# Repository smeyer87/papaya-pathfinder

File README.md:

# Papaya Pathfinder — Personal Build

<div style="text-align: center;">
  
</div>

This is a personal fork of the open-source [Papaya Pathfinder](https://github.com/tronxi/papaya-pathfinder)
rover project, building the **full-size Pathfinder** with custom electronics
and a from-scratch PCB design. It is not a general-purpose reference for the
upstream project — for that (both rover variants, the Android/desktop
controllers, full parts lists, licensing), see the archived
[upstream README](docs/UPSTREAM_README.md).

This fork intentionally does **not** use `pathfinder-mini`,
`android-controller`, or `desktop-controller` — control is via a standard
R/C transmitter/receiver instead.

## Hardware

- **Controller:** ESP32-S3
- **Radio:** RadioMaster ELRS-RP3-V2 receiver + BETAFPV LiteRadio 2 SE
  transmitter (ELRS V3, 2.4 GHz) — not covered by the upstream project;
  see [`docs/elrs-wiring.md`](docs/elrs-wiring.md)
- **Motor Drivers:** 2× BTS7960/IBT_2
- **Motors:** 6× GA25 DC gear motors (3 per side, ganged — one PWM signal
  per side drives all 3 motors on that side simultaneously)
- **Steering:** 4× Miuzei DS3218 servos (front and rear axles only)
- **Power:** LiPo 3S
- **Voltage Regulation:** UBEC 5V/3A (logic) + UBEC 6V/8A (servos)

Full mechanical parts list and 3D-printable files are unchanged from
upstream — see the [3D-Printed Parts table](docs/UPSTREAM_README.md#3d-printed-parts)
and [`pathfinder/3d-models/`](pathfinder/3d-models/).

## Electronics & PCB design (this fork's main addition)

The stock electronics were originally point-to-point soldered onto a
pre-drilled prototyping board. That's being replaced with a custom PCB,
designed via a YAML-first workflow rather than starting cold in KiCad:

- **[`papaya-wiring-layout.yaml`](papaya-wiring-layout.yaml)** — the single
  source of truth for the *entire* electrical system (battery, fuse,
  switch, terminal blocks, motor drivers, UBECs, ESP32, ELRS receiver,
  motors, servos, and the board's own connectors), not just the board.
  Real wire gauges, real terminal numbering, ground loop verified closed.
- **[`pathfinder/kicad/papaya-pcb/`](pathfinder/kicad/papaya-pcb/)** — the
  KiCad 10 project. The schematic is generated (see below), not hand-drawn;
  the layout, copper pours, routing, and 4 corner mounting holes were then
  done by hand and verified with `kicad-cli` DRC (0 violations) and a full
  net-by-net comparison against the YAML.
- **[`pathfinder/kicad/scripts/generate_schematic.py`](pathfinder/kicad/scripts/generate_schematic.py)** —
  reads the wiring YAML and writes a fully-wired starter schematic (every
  component placed, every net labeled), validated against real KiCad 10 with
  zero ERC errors. Re-run it any time the YAML changes:
  ```
  pip install -r pathfinder/kicad/scripts/requirements.txt
  python pathfinder/kicad/scripts/generate_schematic.py
  ```
- **[`pathfinder/kicad/papaya-pcb/gerbers/`](pathfinder/kicad/papaya-pcb/gerbers/)** —
  fabrication output (Gerbers, Excellon drill file, drill map, job file, and
  a zip of the set) for the board revision ordered from OSH Park.

See **[`docs/development-log.md`](docs/development-log.md)** for the full
write-up of how the wiring model, schematic generator, and PCB layout were
built, and the Phase 1 bring-up narrative (including two real hardware
defects found and fixed — see the ADRs below).

**Status: Phase 1 complete** (2026-09-19) — the rover drives under full
ELRS control. See
[`docs/superpowers/specs/2026-08-16-phase1-current-state.md`](docs/superpowers/specs/2026-08-16-phase1-current-state.md)
for the exit-criteria checklist.

## Documentation

- **[`docs/build-guide.md`](docs/build-guide.md) — start here if you're
  building one of these from scratch**: full parts list through
  fabrication, assembly, firmware flashing, and bring-up testing, written
  to route around every mistake made during this build.
- [`docs/build-notes.md`](docs/build-notes.md) — build journal, gap
  analysis vs. the upstream docs, project goals for this fork
- [`docs/elrs-wiring.md`](docs/elrs-wiring.md) — ELRS receiver wiring,
  binding, and RC channel mapping
- [`docs/servo-zeroing.md`](docs/servo-zeroing.md) — flashing firmware and
  validating steering servo centering
- [`docs/development-log.md`](docs/development-log.md) — wiring model,
  KiCad generator, PCB layout, and Phase 1 bring-up narrative
- [`docs/adr/`](docs/adr/) — architecture decision records for two hardware
  defects found post-fabrication (ESP32 header pin trimming; servo header
  ground isolation) and how they were resolved
- [`docs/phase2/inputs/`](docs/phase2/inputs/) — Phase 2 planning input
  templates (missions, capabilities, sensors/compute, platform,
  assumptions/decisions) feeding the Phase 2 design session
- [`docs/UPSTREAM_README.md`](docs/UPSTREAM_README.md) — archived original
  project README (both rover variants, full parts tables, controllers)

## License

This project is licensed under the **Apache License 2.0** — see
[LICENSE](LICENSE). This fork is derived from
[tronxi/papaya-pathfinder](https://github.com/tronxi/papaya-pathfinder);
see [`docs/UPSTREAM_README.md`](docs/UPSTREAM_README.md) for original
project attribution.

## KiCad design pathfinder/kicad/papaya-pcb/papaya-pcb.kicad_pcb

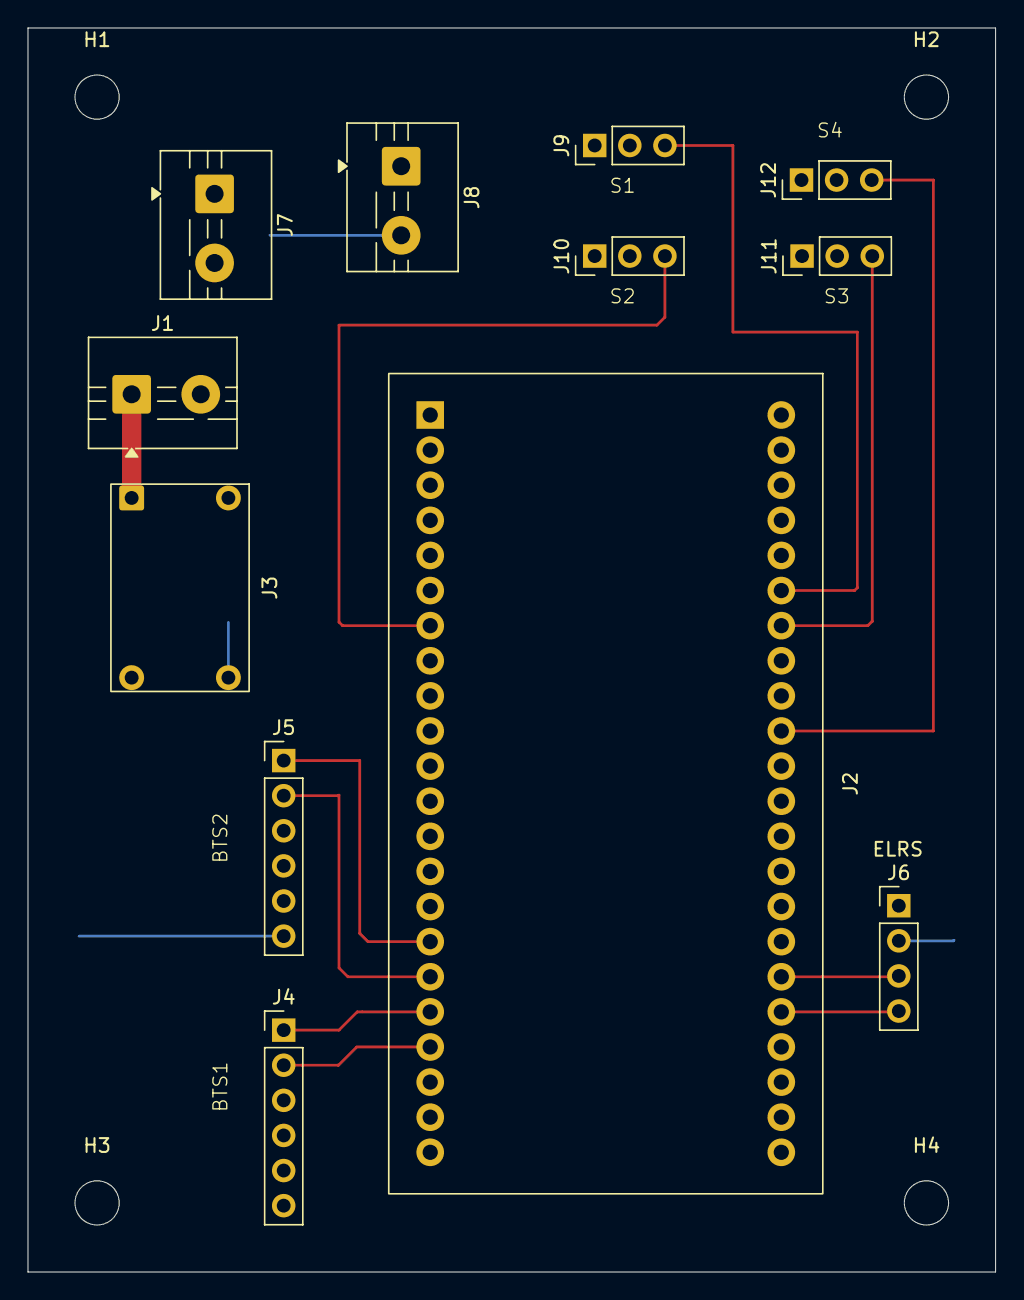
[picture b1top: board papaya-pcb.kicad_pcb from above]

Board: 2 copper layers, 70.0 x 90.0 mm, 16 parts (0 on the bottom side), 14 nets.

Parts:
H1, H2, H3, H4: MountingHole_3.2mm_M3
J1: J1; TerminalBlock_MaiXu_MX126-5.0-02P_1x02_P5.00mm
J2: J_ESP32; ESP32S3_DevKit_2x1x22_split
J3: J_UBEC5V; UBEC_5V_3A_10x15mm
J4: J_BTS1; PinHeader_1x06_BTS_Signal
J5: J_BTS2; PinHeader_1x06_BTS_Signal
J6: J_ELRS; PinHeader_1x04_ELRS
J7: J_GND_MASTER; TerminalBlock_MaiXu_MX126-5.0-02P_1x02_P5.00mm
J8: J_UBEC6V; TerminalBlock_2Pos_UBEC6V
J9: J_S1; PinHeader_1x03_Servo
J10: J_S2; PinHeader_1x03_Servo
J11: J_S3; PinHeader_1x03_Servo
J12: J_S4; PinHeader_1x03_Servo

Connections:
/NET_A_BUS: J1.1 (Main_power_IN(feeds_U2)), J3.INP (U2_5V_IN-POS)
/NET_BTS1_PIN1_RPWM: J2.12 (ESP32_GPIO12-BTS1_pin1_R-PWM(socket)), J4.1 (BTS1_pin1-R-PWM)
/NET_BTS1_PIN2_LPWM: J2.13 (ESP32_GPIO13-BTS1_pin2_L-PWM(socket)), J4.2 (BTS1_pin2-L-PWM)
/NET_BTS2_PIN1_RPWM: J2.10 (ESP32_GPIO10-BTS2_pin1_R-PWM(socket)), J5.1 (BTS2_pin1-R-PWM)
/NET_BTS2_PIN2_LPWM: J2.11 (ESP32_GPIO11-BTS2_pin2_L-PWM(socket)), J5.2 (BTS2_pin2-L-PWM)
/NET_BUS_5V: J2.5V (ESP32_5V_IN_(socket_pin)), J3.OUTP (U2_5V_OUT_POS), J4.3 (BTS1_pin3-R-EN(5V)), J4.4 (BTS1_pin4-L-EN(5V)), J4.7 (BTS1_pin7-VCC(5V)), J5.3 (BTS2_pin3-R-EN(5V)), J5.4 (BTS2_pin4-L-EN(5V)), J5.7 (BTS2_pin7-VCC(5V)), J6.VCC (ELRS_VCC(5V))
/NET_BUS_6V: J8.OUTP (U1_6V_OUT(servo_+)), J9.PWR (S1_pin2-PWR(red)), J10.PWR (S2_pin2-PWR(red)), J11.PWR (S3_pin2-PWR(red)), J12.PWR (S4_pin2-PWR(red))
/NET_B_BUS: J1.2 (J1.2), J2.GND_1 (ESP32_ground,_near_5V_IN_(socket_pin)), J2.GND_2 (ESP32_ground_near_TX(socket_pin)), J3.INN (U2_5V_IN-NEG), J3.OUTN (U2_5V_OUT-NEG), J4.8 (BTS1_pin8-GND), J5.8 (BTS2_pin8-GND), J6.GND (ELRS_GND), J7.1 (Master_GND_OUT(to_B14)_1), J8.OUTN (U1_6V_OUT(servo_GND)), J9.GND (S1_pin1-GND(black)), J10.GND (S2_pin1-GND(black)), J11.GND (S3_pin1-GND(black)), J12.GND (S4_pin1-GND(black))
/NET_ELRS_RX: J2.21 (ESP32_GPIO21-ELRS_RX_white(socket)), J6.RX (ELRS_RX(white))
/NET_ELRS_TX: J2.47 (ESP32_GPIO47-ELRS_TX_green(socket)), J6.TX (ELRS_TX(green))
/NET_S1_SIG: J2.42 (ESP32_GPIO42-S1-RF_signal(socket)), J9.SIG (S1_pin3-SIG(white))
/NET_S2_SIG: J2.7 (ESP32_GPIO7-S2-LF-signal(socket)), J10.SIG (S2_pin3-SIG(white))
/NET_S3_SIG: J2.41 (ESP32_GPIO41-S3-RR_signal(socket)), J11.SIG (S3_pin3-SIG(white))
/NET_S4_SIG: J2.38 (ESP32_GPIO38-S4-LR_signal(socket)), J12.SIG (S4_pin3-SIG(white))
